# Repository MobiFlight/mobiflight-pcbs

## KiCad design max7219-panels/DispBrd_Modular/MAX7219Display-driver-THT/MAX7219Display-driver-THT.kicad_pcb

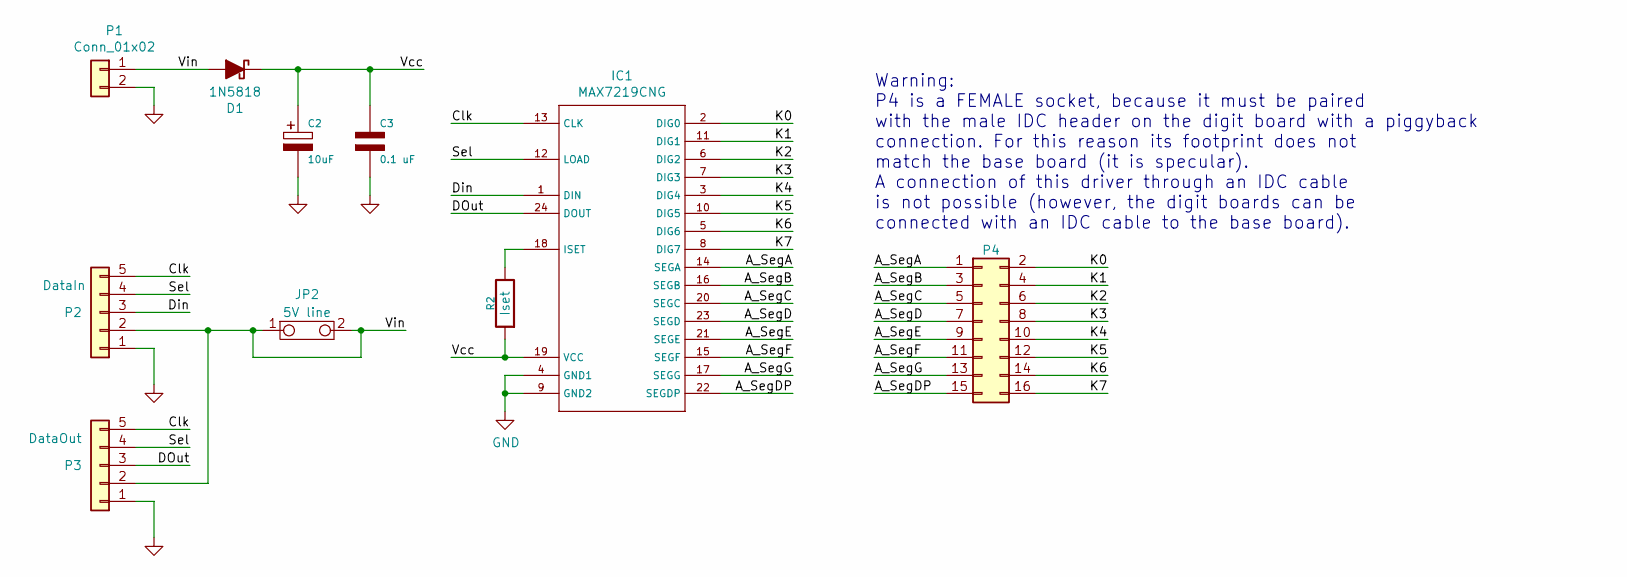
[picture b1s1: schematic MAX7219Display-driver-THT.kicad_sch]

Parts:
C2: 10uF; CP_Radial_D5.0mm_P2.50mm
C3: 0.1 uF; C_1206_3216Metric_Pad1.42x1.75mm_HandSolder
D1: 1N5818; D_SMA_Handsoldering
IC1: MAX7219CNG; DIP-24_W7.62mm_Socket
JP2: 5V line; SolderJumper-2_P1.3mm_Bridged_Pad1.0x1.5mm
P1: Conn_01x02; PinHeader_1x02_P2.54mm_Vertical
P2: DataIn; JST_XH_B5B-XH-A_1x05_P2.50mm_Vertical
P3: DataOut; JST_XH_B5B-XH-A_1x05_P2.50mm_Vertical
P4: Conn_02x08_Odd_Even; PinSocket_2x08_P2.54mm_Vertical
R2: Iset; R_Axial_DIN0207_L6.3mm_D2.5mm_P10.16mm_Horizontal

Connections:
/A_SegA: IC1.14 (SEGA), P4.1
/A_SegB: IC1.16 (SEGB), P4.3
/A_SegC: IC1.20 (SEGC), P4.5
/A_SegD: IC1.23 (SEGD), P4.7
/A_SegDP: IC1.22 (SEGDP), P4.15
/A_SegE: IC1.21 (SEGE), P4.9
/A_SegF: IC1.15 (SEGF), P4.11
/A_SegG: IC1.17 (SEGG), P4.13
/Clk: IC1.13 (CLK), P2.5, P3.5
/DOut: IC1.24 (DOUT), P3.3
/Din: IC1.1 (DIN), P2.3
/K0: IC1.2 (DIG0), P4.2
/K1: IC1.11 (DIG1), P4.4
/K2: IC1.6 (DIG2), P4.6
/K3: IC1.7 (DIG3), P4.8
/K4: IC1.3 (DIG4), P4.10
/K5: IC1.10 (DIG5), P4.12
/K6: IC1.5 (DIG6), P4.14
/K7: IC1.8 (DIG7), P4.16
/Sel: IC1.12 (LOAD), P2.4, P3.4
/Vcc: C2.1, C3.1, D1.1 (K), IC1.19 (VCC), R2.1
/Vin: D1.2 (A), JP2.1, JP2.2, P1.1, P2.2, P3.2
GND: C2.2, C3.2, IC1.4 (GND1), IC1.9 (GND2), P1.2, P2.1, P3.1
unnamed: IC1.18 (ISET), R2.2

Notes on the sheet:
Warning: P4 is a FEMALE socket, because it must be paired with the male IDC header on the digit board with a piggyback connection. For this reason its footprint does not match the base board (it is specular). A connection of this driver through an IDC cable is not possible (however, the digit board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

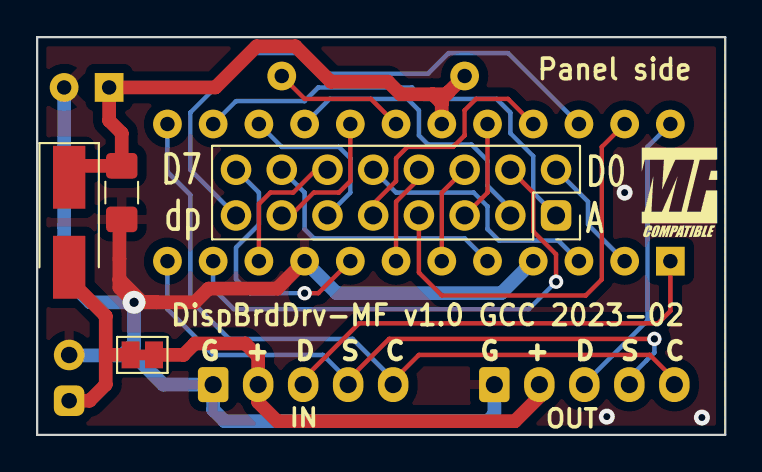
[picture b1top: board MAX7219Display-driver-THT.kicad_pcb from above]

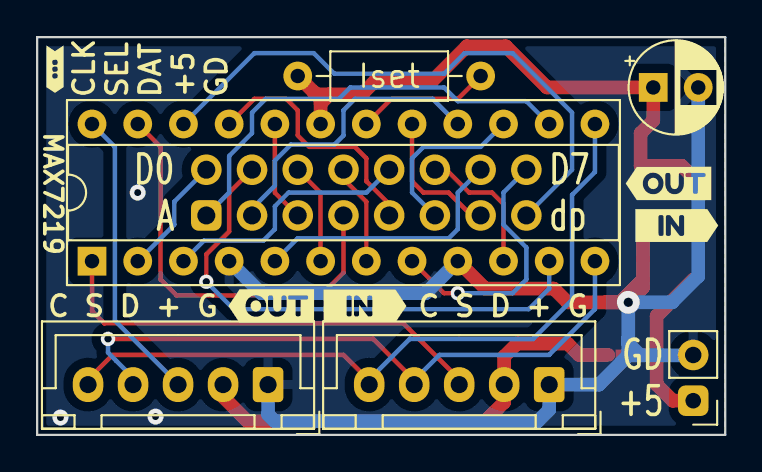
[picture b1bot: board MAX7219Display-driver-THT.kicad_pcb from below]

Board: 2 copper layers, 38.2 x 22.1 mm, 15 parts (11 on the bottom side), 24 nets.

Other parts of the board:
kibuzzard-6403BB05: G***; kibuzzard-6403BB05
kibuzzard-6405E13D: G***; kibuzzard-6405E13D
kibuzzard-6405E14C: G***; kibuzzard-6405E14C
kibuzzard-6405E134: G***; kibuzzard-6405E134
kibuzzard-6405E146: G***; kibuzzard-6405E146

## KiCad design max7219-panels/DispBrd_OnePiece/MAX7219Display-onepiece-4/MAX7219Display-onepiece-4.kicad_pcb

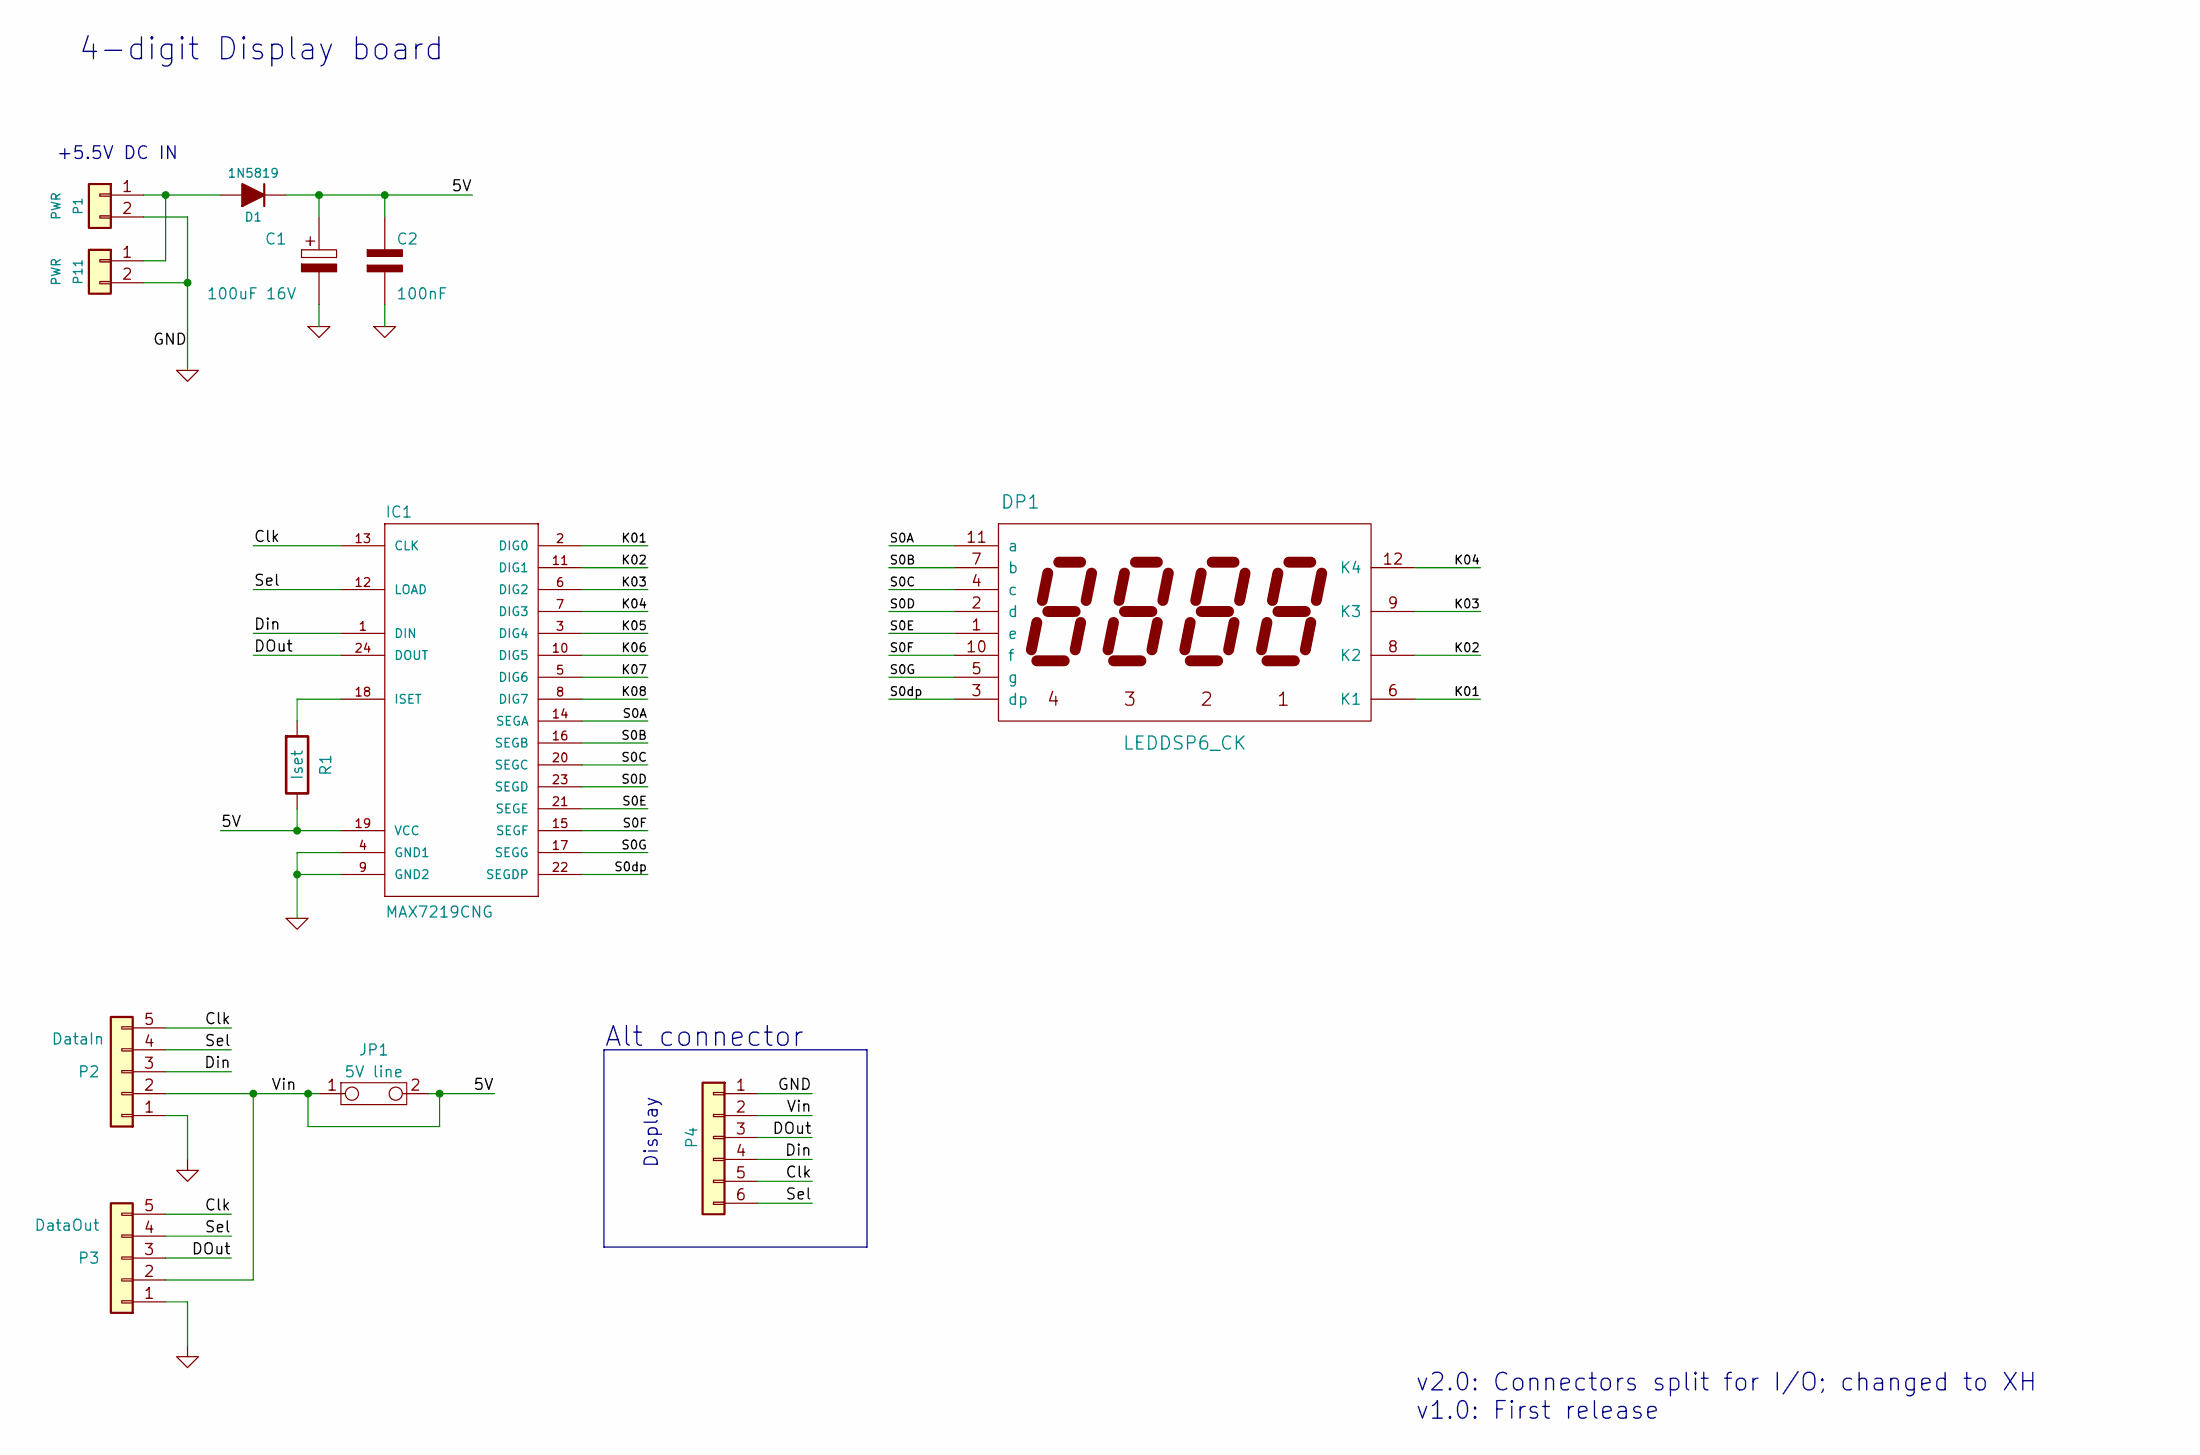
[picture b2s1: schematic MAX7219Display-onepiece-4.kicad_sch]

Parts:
C1: 100uF 16V; CP_Radial_D5.0mm_P2.50mm
C2: 100nF; C_1206_3216Metric_Pad1.33x1.80mm_HandSolder
D1: 1N5819; D_SMA_Handsoldering
DP1: LEDDSP6_CK; Disp7s4x_036
IC1: MAX7219CNG; DIP-24_W7.62mm_Socket
JP1: 5V line; SolderJumper-2_P1.3mm_Bridged_Pad1.0x1.5mm
P1: PWR; PinHeader_1x02_P2.54mm_Vertical
P2: DataIn; JST_XH_B5B-XH-A_1x05_P2.50mm_Vertical
P3: DataOut; JST_XH_B5B-XH-A_1x05_P2.50mm_Vertical
P4: CONN-6; PinHeader_1x06_P2.54mm_Vertical
P11: PWR; HDR2-3.50+3.81mm
R1: Iset; R_Axial_DIN0207_L6.3mm_D2.5mm_P10.16mm_Horizontal

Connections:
/5V: C1.1, C2.1, D1.1 (K), IC1.19 (VCC), JP1.1, JP1.2, P2.2, P3.2, P4.2, R1.2
/Clk: IC1.13 (CLK), P2.5, P3.5, P4.5
/DOut: IC1.24 (DOUT), P3.3, P4.3
/Din: IC1.1 (DIN), P2.3, P4.4
/K01: DP1.6 (K1), IC1.2 (DIG0)
/K02: DP1.8 (K2), IC1.11 (DIG1)
/K03: DP1.9 (K3), IC1.6 (DIG2)
/K04: DP1.12 (K4), IC1.7 (DIG3)
/K05: IC1.3 (DIG4)
/K06: IC1.10 (DIG5)
/K07: IC1.5 (DIG6)
/K08: IC1.8 (DIG7)
/S0A: DP1.11 (a), IC1.14 (SEGA)
/S0B: DP1.7 (b), IC1.16 (SEGB)
/S0C: DP1.4 (c), IC1.20 (SEGC)
/S0D: DP1.2 (d), IC1.23 (SEGD)
/S0E: DP1.1 (e), IC1.21 (SEGE)
/S0F: DP1.10 (f), IC1.15 (SEGF)
/S0G: DP1.5 (g), IC1.17 (SEGG)
/S0dp: DP1.3 (dp), IC1.22 (SEGDP)
/Sel: IC1.12 (LOAD), P2.4, P3.4, P4.6
GND: C1.2, C2.2, IC1.4 (GND1), IC1.9 (GND2), P1.2, P2.1, P3.1, P4.1, P11.2
unnamed: D1.2 (A), P1.1, P11.1
unnamed: IC1.18 (ISET), R1.1

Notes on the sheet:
+5.5V DC IN
Alt connector
v2.0: Connectors split for I/O; changed to XH v1.0: First release
4-digit Display board
Display

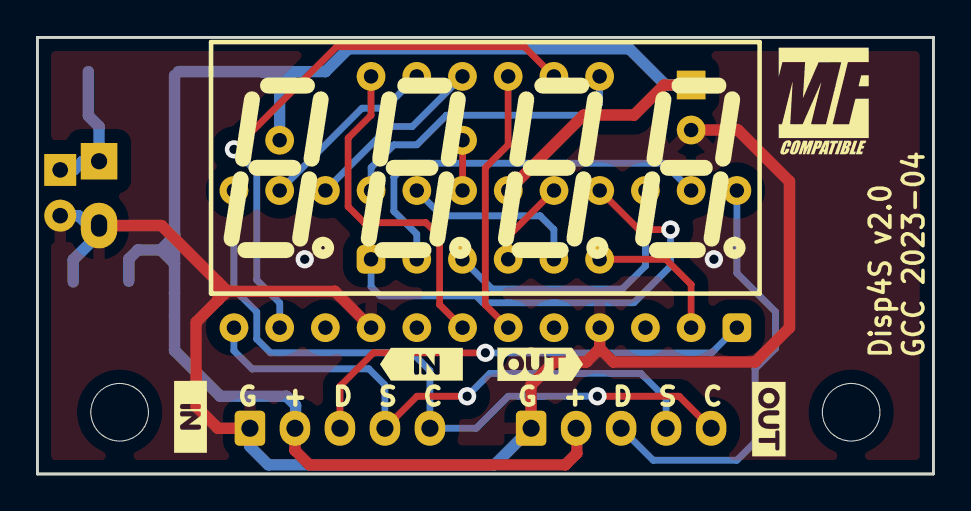
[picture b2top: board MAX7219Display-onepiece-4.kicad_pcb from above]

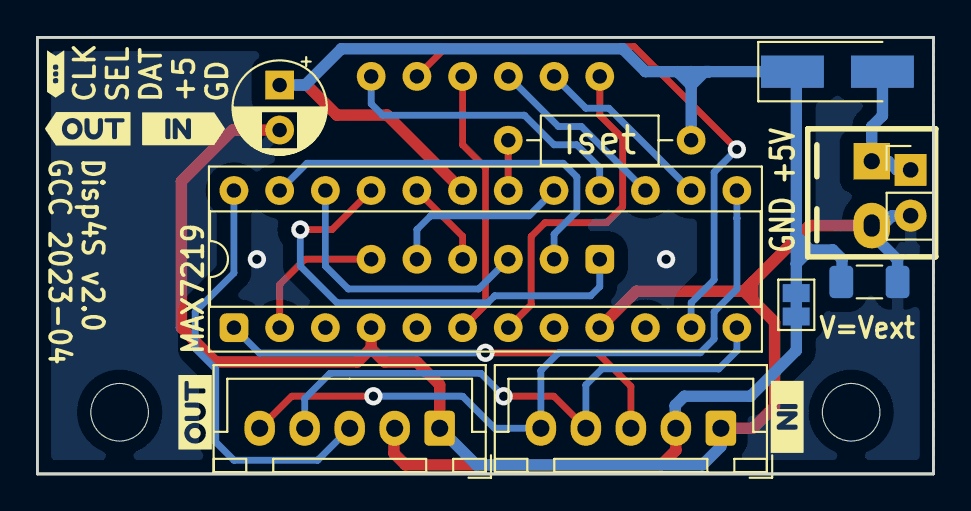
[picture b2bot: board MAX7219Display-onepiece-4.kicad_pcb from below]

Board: 2 copper layers, 49.8 x 24.3 mm, 22 parts (15 on the bottom side), 20 nets.

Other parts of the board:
H1, H2: CONN_1; MountingHole_3.2mm_M3
kibuzzard-643D9E97: G***; kibuzzard-643D9E97
kibuzzard-643D9EA5: G***; kibuzzard-643D9EA5
kibuzzard-643DAD0B: G***; kibuzzard-643DAD0B
kibuzzard-643DAD14, kibuzzard-643DAD14#2: G***; kibuzzard-643DAD14
kibuzzard-643DAD66: G***; kibuzzard-643DAD66
kibuzzard-6403BB05: G***; kibuzzard-6403BB05
kibuzzard-6405E14C: G***; kibuzzard-6405E14C
kibuzzard-6405E146: G***; kibuzzard-6405E146

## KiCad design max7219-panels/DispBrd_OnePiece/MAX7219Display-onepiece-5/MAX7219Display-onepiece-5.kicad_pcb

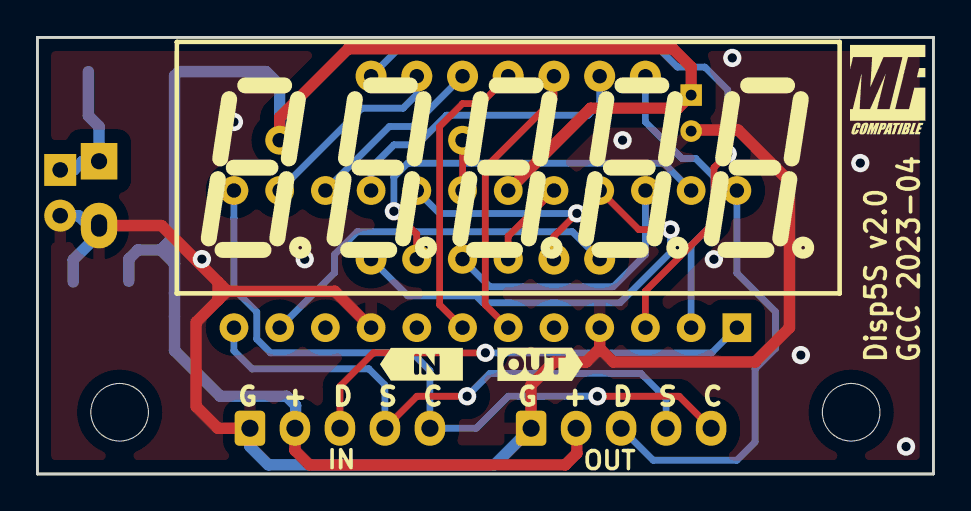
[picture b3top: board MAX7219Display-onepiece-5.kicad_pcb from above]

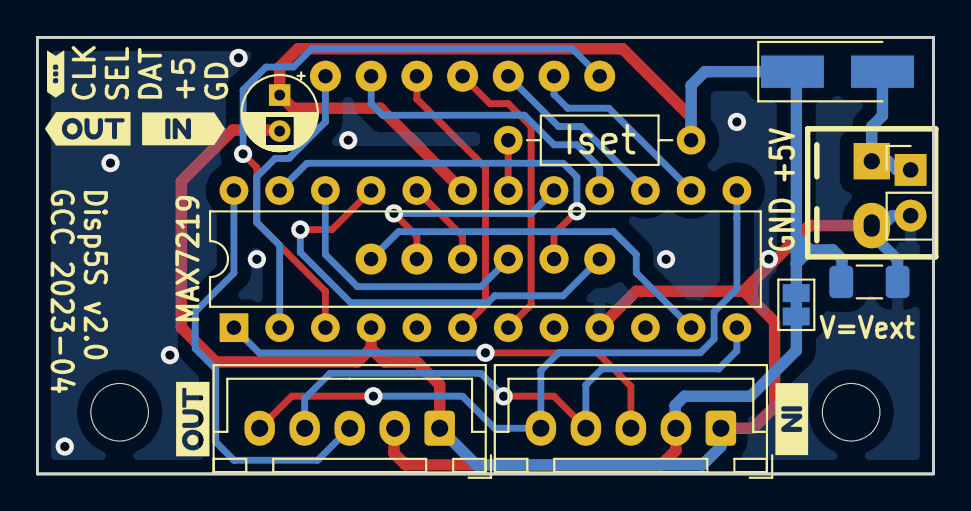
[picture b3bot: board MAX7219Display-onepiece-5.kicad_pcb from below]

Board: 2 copper layers, 49.8 x 24.3 mm, 20 parts (15 on the bottom side), 21 nets.

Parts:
C1: 100uF 16V; CP_Radial_D4.0mm_P2.00mm
C2: 100nF; C_1206_3216Metric_Pad1.33x1.80mm_HandSolder
D1: 1N5819; D_SMA_Handsoldering
DP3: LEDDSP6_CK; Disp7s5x_036
H1, H2: CONN_1; MountingHole_3.2mm_M3
IC1: MAX7219CNG; DIP-24_W7.62mm
JP1: 5V line; SolderJumper-2_P1.3mm_Bridged_Pad1.0x1.5mm
P1: PWR; PinHeader_1x02_P2.54mm_Vertical
P2: DataIn; JST_XH_B5B-XH-A_1x05_P2.50mm_Vertical
P3: DataOut; JST_XH_B5B-XH-A_1x05_P2.50mm_Vertical
P11: PWR; HDR2-3.50+3.81mm
R1: Iset; R_Axial_DIN0207_L6.3mm_D2.5mm_P10.16mm_Horizontal
kibuzzard-643D9E97: G***; kibuzzard-643D9E97
kibuzzard-643D9EA5: G***; kibuzzard-643D9EA5
kibuzzard-643DAA36: G***; kibuzzard-643DAA36
kibuzzard-643DAA60: G***; kibuzzard-643DAA60
kibuzzard-6403BB05: G***; kibuzzard-6403BB05
kibuzzard-6405E14C: G***; kibuzzard-6405E14C
kibuzzard-6405E146: G***; kibuzzard-6405E146

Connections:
/Clk: IC1.13 (CLK), P2.5, P3.5
/DOut: IC1.24 (DOUT), P3.3
/Din: IC1.1 (DIN), P2.3
/K01: DP3.8 (K1), IC1.2 (DIG0)
/K02: DP3.6 (K2), IC1.11 (DIG1)
/K03: DP3.10 (K3), IC1.6 (DIG2)
/K04: DP3.11 (K4), IC1.7 (DIG3)
/K05: DP3.14 (K5), IC1.3 (DIG4)
/S0A: DP3.13 (a), IC1.14 (SEGA)
/S0B: DP3.9 (b), IC1.16 (SEGB)
/S0C: DP3.4 (c), IC1.20 (SEGC)
/S0D: DP3.2 (d), IC1.23 (SEGD)
/S0E: DP3.1 (e), IC1.21 (SEGE)
/S0F: DP3.12 (f), IC1.15 (SEGF)
/S0G: DP3.5 (g), IC1.17 (SEGG)
/S0dp: DP3.3 (dp), IC1.22 (SEGDP)
/Sel: IC1.12 (LOAD), P2.4, P3.4
/Vin: C1.1, C2.1, D1.1 (K), IC1.19 (VCC), JP1.1, JP1.2, P2.2, P3.2, R1.2
GND: C1.2, C2.2, IC1.4 (GND1), IC1.9 (GND2), P1.2, P2.1, P3.1, P11.2
unnamed: D1.2 (A), P1.1, P11.1
unnamed: IC1.18 (ISET), R1.1

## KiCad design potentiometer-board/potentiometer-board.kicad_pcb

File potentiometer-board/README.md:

# Potentiometer board

The potentiometer board fits the same form factor and 20x20mm mounting hole pattern 
as the popular dual encoder board. 

This board features a soldering footprint for an Alps RK09 style potentiometer (the one that looks similar
to common EC11-style rotary encoders) and a three pin JST XH connector for the wires.

This repository contains the KiCad project files and also a gerber zip that can be used to manufacture the board.
But if you are interested in this board, you can also find it in the 
[MobiFlight Community Shop](https://shop.mobiflight.com/product/potentiometer-bundle) bundled with a resin printed
knob set.

Designed by Tuomas Kuosmanen, December 2024
The RK09 potentiometer STEP file was 
[created and shared on GrabCAD by Mart Berghs](https://grabcad.com/library/potentiometer-30).

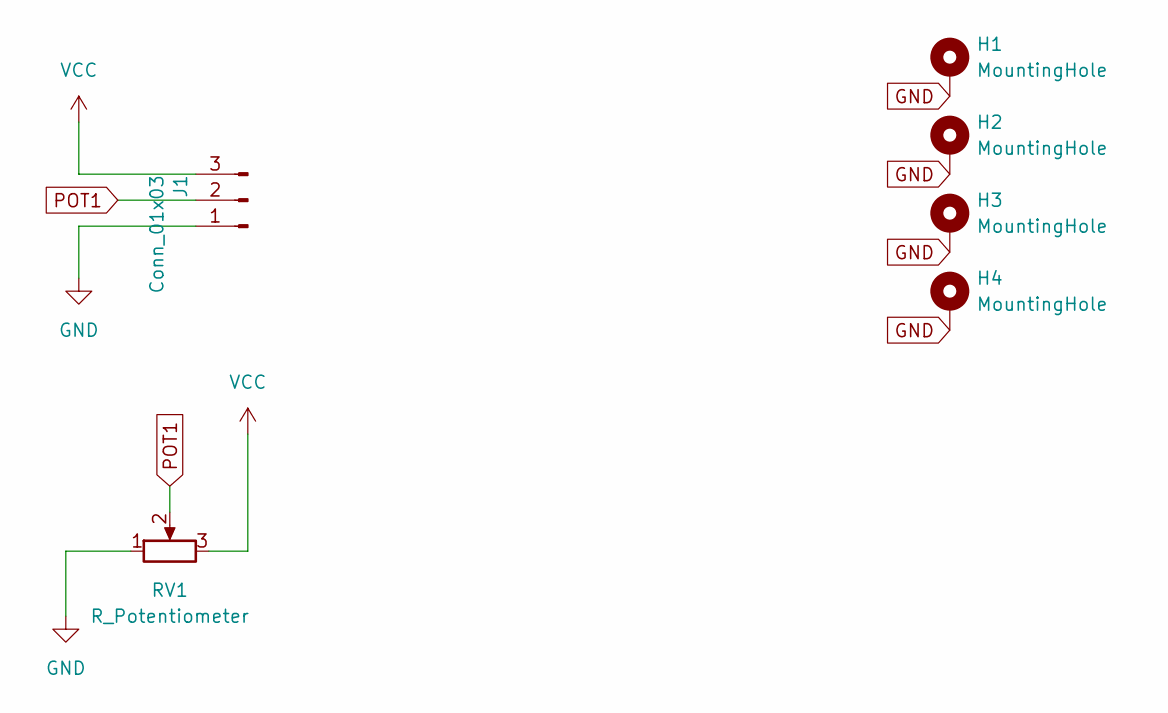
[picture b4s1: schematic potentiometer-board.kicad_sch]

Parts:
H1, H2, H3, H4: MountingHole; MountingHole_3.2mm_M3_ISO14580_Pad_TopBottom
J1: Conn_01x03; JST_XH_B3B-XH-A_1x03_P2.50mm_Vertical; LCSC C144394
RV1: R_Potentiometer; Potentiometer_Alps_RK09K_Single_Vertical

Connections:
GND: H1.1, H2.1, H3.1, H4.1, J1.1, RV1.1
POT1: J1.2, RV1.2
VCC: J1.3, RV1.3

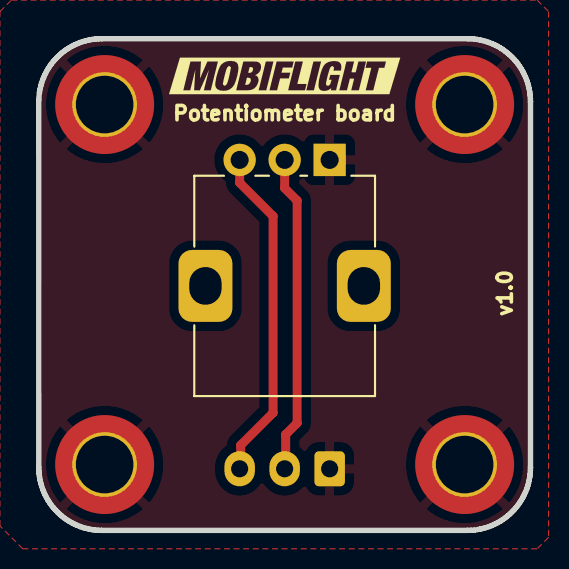
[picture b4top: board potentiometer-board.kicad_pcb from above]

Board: 2 copper layers, 27.3 x 27.3 mm, 7 parts (1 on the bottom side), 3 nets.

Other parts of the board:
kibuzzard-6380ACF0: G***; kibuzzard-6380ACF0

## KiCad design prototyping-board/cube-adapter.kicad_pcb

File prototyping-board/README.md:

# MobiFlight Prototyping Board
The MobiFlight Prototyping Board is a breakout board to learn and experiment with the different input and output devices that are supported by MobiFlight.
The board uses XH JST connectors of different sizes depending on the type of device. These connectors ensure a secure connection and correct orientation of the plugs.

The MobiFlight Prototyping Board is compatible with Arduino Mega 2560 Pro Mini that is attached to the back of the board.

There are two configurations available (latest v2.1):
* Standard - [prototyping-board.mfmc](prototyping-board.mfmc)

  All buttons from `Button 01` to `Button-06` are available, and `Stepper 1` and `Stepper 2` can be both used for steppers 
* Multiplexer - [prototyping-board.multiplexer.mfmc](prototyping-board.multiplexer.mfmc)

  using Stepper 2 as Multiplexer 1 connection, and Button 1 and Button 2 for the signal channels. See [Multiplexer Breakout Board](../breakout-multiplexer/README.md) for more information.

The board is updated based on user feedback, please see the section [older versions](#older-versions) of the config file.
## Devices overview

### Button 1 - 6
Simple buttons that connect with just two wires.

Left pin is Ground, right pin is VCC.

**IMPORTANT** Button 6 is shared with 4th Encoder Push Button

### LEDs 1 - 6
All LEDs are using PWM enabled pins and can be dimmed in MobiFlight.
It is recommended to add an apropriate resistor for you LED. 
[More information about LED output devices](https://docs.mobiflight.com/devices/led/).

Left pin is Ground, right pin is VCC.

### Switch 1 - 5 (On-On)
Connector is designed for On-On switches, two or three position switches.
[More information about buttons and switches](https://docs.mobiflight.com/devices/button-switch/).

* Left pin is GND
* middle pin is Button 1 
* right pin is Button 2

### Switch 6 - 10 (On-On)
Connector is designed for On-On switches, two or three position switches.
[More information about buttons and switches](https://docs.mobiflight.com/devices/button-switch/).

* left pin is GND,
* middle pin is Button 1, 
* right pin is Button 2.

### 7-Segment 1
Connect a 7219MAX-chip based board to this pin.
[More information about 7-segment displays](https://docs.mobiflight.com/devices/seven-segment-display/).

* 1st pin GND,
* 2nd pin VCC,
* 3rd pin DIN,
* 4th pin CS,
* 5th pin CLK

### Encoder 1-4
Connect a Encoder with Push Button function.
[More information about rotary encoders](https://docs.mobiflight.com/devices/encoder/).

* 1st pin GND
* 2nd pin Left Pin (A)
* 3rd pin Right Pin (B)
* 4th pin Push Button

**IMPORTANT** 4th Encoder Push Button is shared with Button 6

### Pot 1 - 3
Connect a Potentiometer or other analog input device.
[More information about potentiometers](https://docs.mobiflight.com/devices/potentiometer/).

* 1st pin GND
* 2nd pin Signal
* 3rd pin VCC

### Shift-Register 1-2
Connect an output shift register.
[More information about output shift registers](https://docs.mobiflight.com/devices/output-shift-register/).

* 1st pin GND
* 2nd pin VCC
* 3rd pin SPI (Latch)
* 4th pin SPI (Clock)
* 5th pin SPI (Data)

### Servo 1-2
Connect a servo. [More information about servos](https://docs.mobiflight.com/devices/servo/).

* 1st pin GND 
* 2nd pin VCC
* 3rd pin DIN

### Stepper 1-2
Connect a stepper. [More information about stepper motors](https://docs.mobiflight.com/devices/stepper-motor/).

* 1st pin GND
* 2nd pin VCC
* 3rd pin Pin1 
* 4th pin Pin2
* 5th pin Pin3
* 6th pin Pin4

Use an additional button pin for the Auto-Zero function.

### LCD Display 1-2
Connect a LCD Display. [More information about LCD displays](https://docs.mobiflight.com/devices/lcd/).

* 1st pin GND
* 2nd pin VCC
* 3rd pin I2C - SDA
* 4th pin I2C - SCL

## Schematic

## Bottom side

## Older versions
For older versions please use the following files:
* 2.0 - [prototyping-board-2.0.mfmc](prototyping-board-2.0.mfmc)

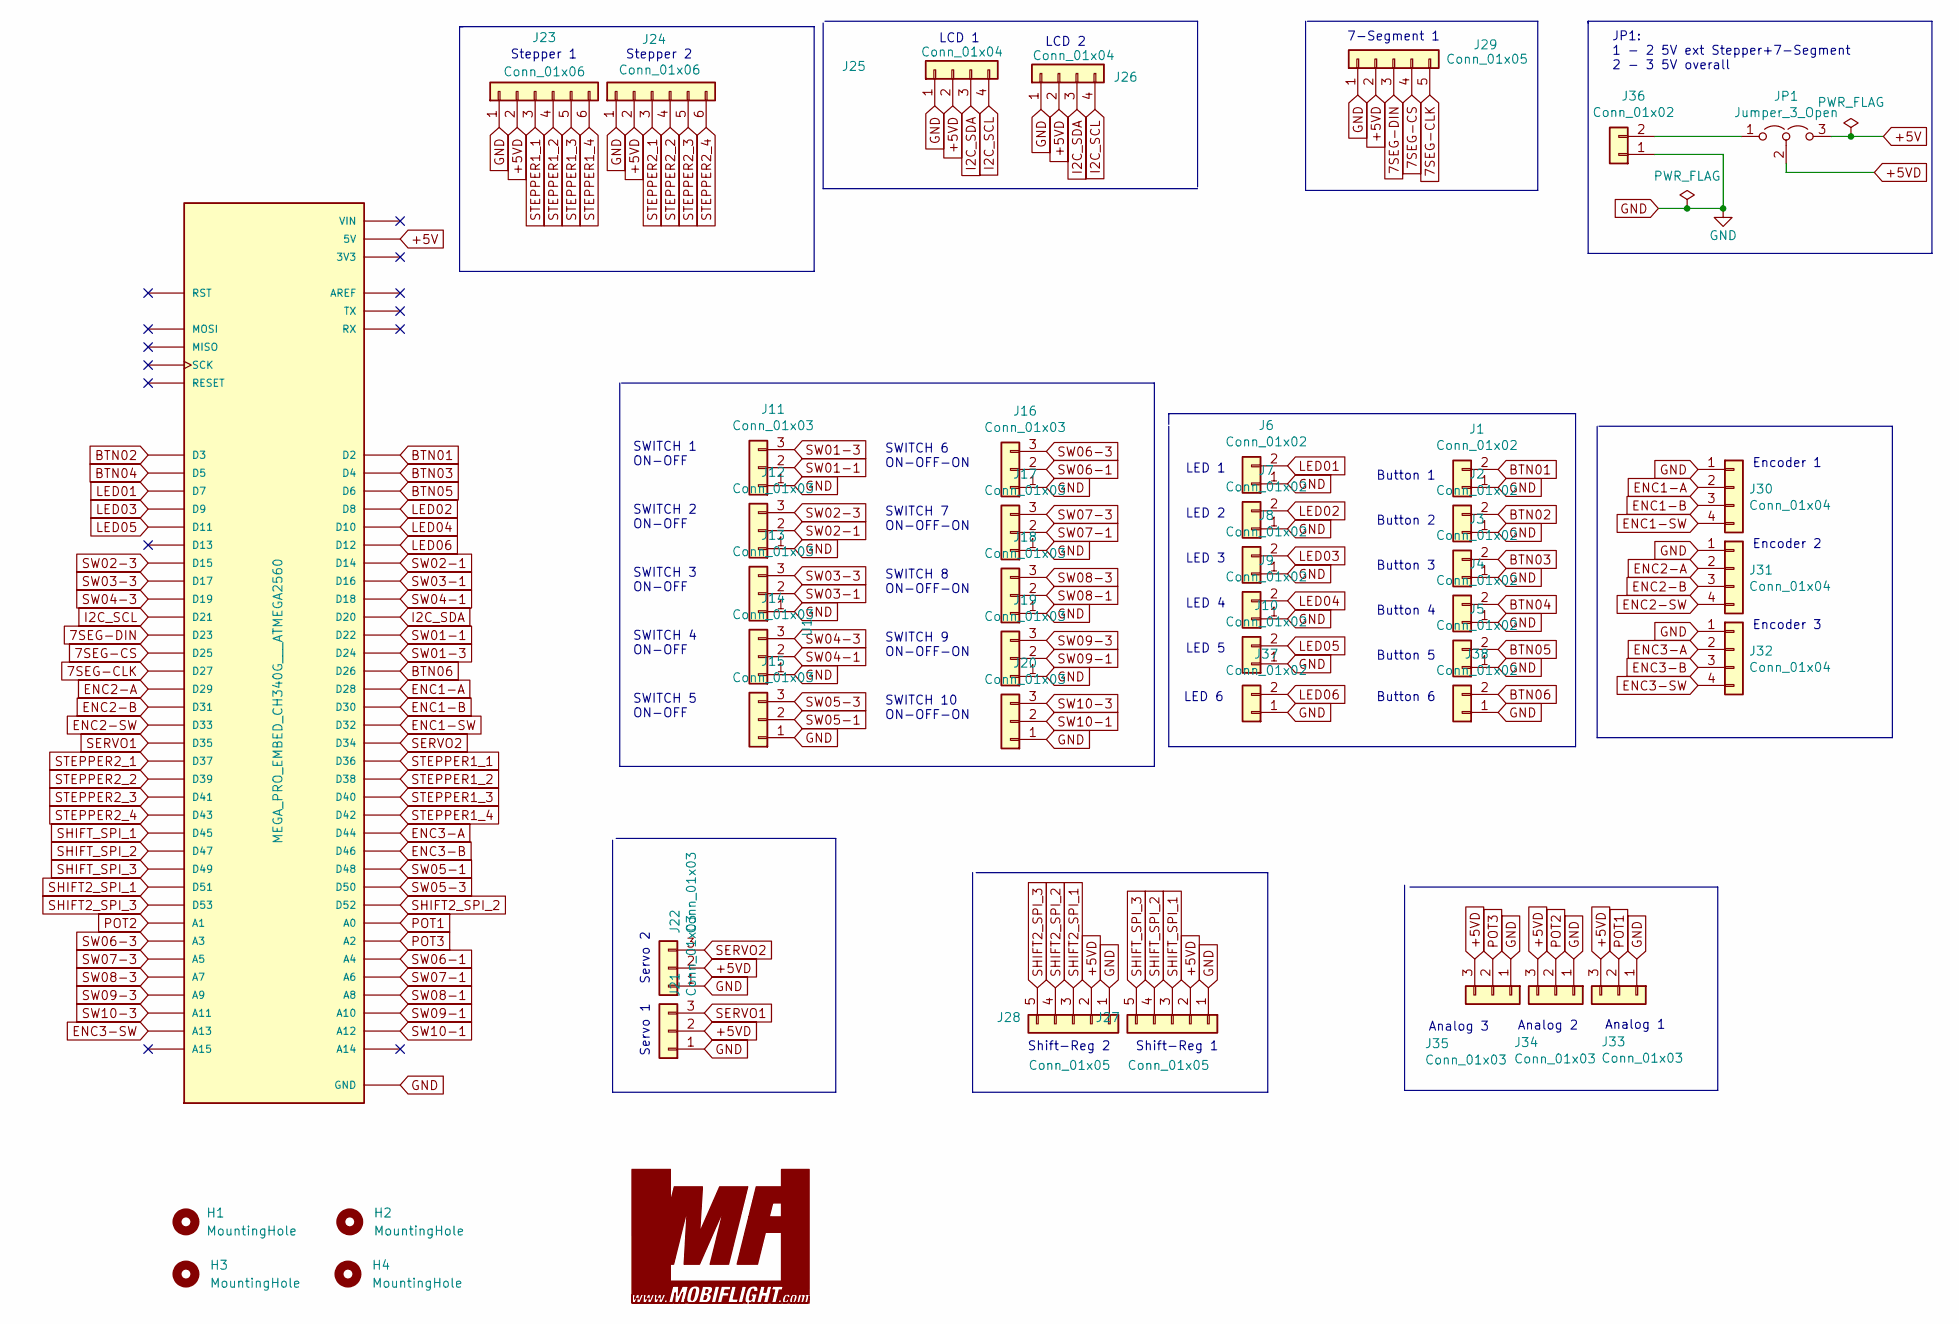
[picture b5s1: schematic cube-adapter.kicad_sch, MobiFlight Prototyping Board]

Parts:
H1, H2, H3, H4: MountingHole; MountingHole_3.5mm
J1, J2, J3, J4, J5, J6, J7, J8, J9, J10, J36, J37, J38: Conn_01x02; JST_XH_B2B-XH-A_1x02_P2.50mm_Vertical
J11, J12, J13, J14, J15, J16, J17, J18, J19, J20, J21, J22, J33, J34, J35: Conn_01x03; JST_XH_B3B-XH-A_1x03_P2.50mm_Vertical
J23, J24: Conn_01x06; JST_XH_B6B-XH-A_1x06_P2.50mm_Vertical
J25, J26, J30, J31, J32: Conn_01x04; JST_XH_B4B-XH-A_1x04_P2.50mm_Vertical
J27, J28, J29: Conn_01x05; JST_XH_B5B-XH-A_1x05_P2.50mm_Vertical
JP1: Jumper_3_Open; PinHeader_1x03_P2.54mm_Vertical
U1: MEGA_PRO_EMBED_CH340G___ATMEGA2560; _ATMEGA2560; PARTREV 12/May/2017

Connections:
7SEG-CLK: J29.5, U1.D27
7SEG-CS: J29.4, U1.D25
7SEG-DIN: J29.3, U1.D23
+5V: JP1.3 (B), U1.5V_1 (5V), U1.5V_2 (5V), U1.5V_3 (5V)
+5VD: J21.2, J22.2, J23.2, J24.2, J25.2, J26.2, J27.2, J28.2, J29.2, J33.3, J34.3, J35.3, JP1.2 (C)
BTN01: J1.2, U1.D2
BTN02: J2.2, U1.D3
BTN03: J3.2, U1.D4
BTN04: J4.2, U1.D5
BTN05: J5.2, U1.D6
BTN06: J38.2, U1.D26
ENC1-A: J30.2, U1.D28
ENC1-B: J30.3, U1.D30
ENC1-SW: J30.4, U1.D32
ENC2-A: J31.2, U1.D29
ENC2-B: J31.3, U1.D31
ENC2-SW: J31.4, U1.D33
ENC3-A: J32.2, U1.D44
ENC3-B: J32.3, U1.D46
ENC3-SW: J32.4, U1.A13
GND: J1.1, J2.1, J3.1, J4.1, J5.1, J6.1, J7.1, J8.1, J9.1, J10.1, J11.1, J12.1, J13.1, J14.1, J15.1, J16.1, J17.1, J18.1, J19.1, J20.1, J21.1, J22.1, J23.1, J24.1, J25.1, J26.1, J27.1, J28.1, J29.1, J30.1, J31.1, J32.1, J33.1, J34.1, J35.1, J36.1, J37.1, J38.1, U1.GND_1 (GND), U1.GND_2 (GND), U1.GND_3 (GND)
I2C_SCL: J25.4, J26.4, U1.D21
I2C_SDA: J25.3, J26.3, U1.D20
LED01: J6.2, U1.D7
LED02: J7.2, U1.D8
LED03: J8.2, U1.D9
LED04: J9.2, U1.D10
LED05: J10.2, U1.D11
LED06: J37.2, U1.D12
unnamed: J36.2, JP1.1 (A)
POT1: J33.2, U1.A0
POT2: J34.2, U1.A1
POT3: J35.2, U1.A2
SERVO1: J21.3, U1.D35
SERVO2: J22.3, U1.D34
SHIFT2_SPI_1: J28.3, U1.D51
SHIFT2_SPI_2: J28.4, U1.D52
SHIFT2_SPI_3: J28.5, U1.D53
SHIFT_SPI_1: J27.3, U1.D45
SHIFT_SPI_2: J27.4, U1.D47
SHIFT_SPI_3: J27.5, U1.D49
STEPPER1_1: J23.3, U1.D36
STEPPER1_2: J23.4, U1.D38
STEPPER1_3: J23.5, U1.D40
STEPPER1_4: J23.6, U1.D42
STEPPER2_1: J24.3, U1.D37
STEPPER2_2: J24.4, U1.D39
STEPPER2_3: J24.5, U1.D41
STEPPER2_4: J24.6, U1.D43
SW01-1: J11.2, U1.D22
SW01-3: J11.3, U1.D24
SW02-1: J12.2, U1.D14
SW02-3: J12.3, U1.D15
SW03-1: J13.2, U1.D16
SW03-3: J13.3, U1.D17
SW04-1: J14.2, U1.D18
SW04-3: J14.3, U1.D19
SW05-1: J15.2, U1.D48
SW05-3: J15.3, U1.D50
SW06-1: J16.2, U1.A4
SW06-3: J16.3, U1.A3
SW07-1: J17.2, U1.A6
SW07-3: J17.3, U1.A5
SW08-1: J18.2, U1.A8
SW08-3: J18.3, U1.A7
SW09-1: J19.2, U1.A10
SW09-3: J19.3, U1.A9
SW10-1: J20.2, U1.A12
SW10-3: J20.3, U1.A11

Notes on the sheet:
SWITCH 6 ON-OFF-ON
Button 6
Servo 1
Analog 3
LCD 2
LED 5
Shift-Reg 1
LED 4
SWITCH 4 ON-OFF
Encoder 3
Button 1
Analog 1
JP1: 1 - 2 5V ext Stepper+7-Segment 2 - 3 5V overall
SWITCH 9 ON-OFF-ON
7-Segment 1
Encoder 2
SWITCH 3 ON-OFF
Analog 2
Servo 2
Encoder 1
SWITCH 8 ON-OFF-ON
LED 1
Stepper 1
Button 3
SWITCH 2 ON-OFF
LED 2
SWITCH 10 ON-OFF-ON
Shift-Reg 2
LED 3
SWITCH 1 ON-OFF
LED 6
Button 5
Button 2
SWITCH 5 ON-OFF
Button 4
LCD 1
Stepper 2
SWITCH 7 ON-OFF-ON

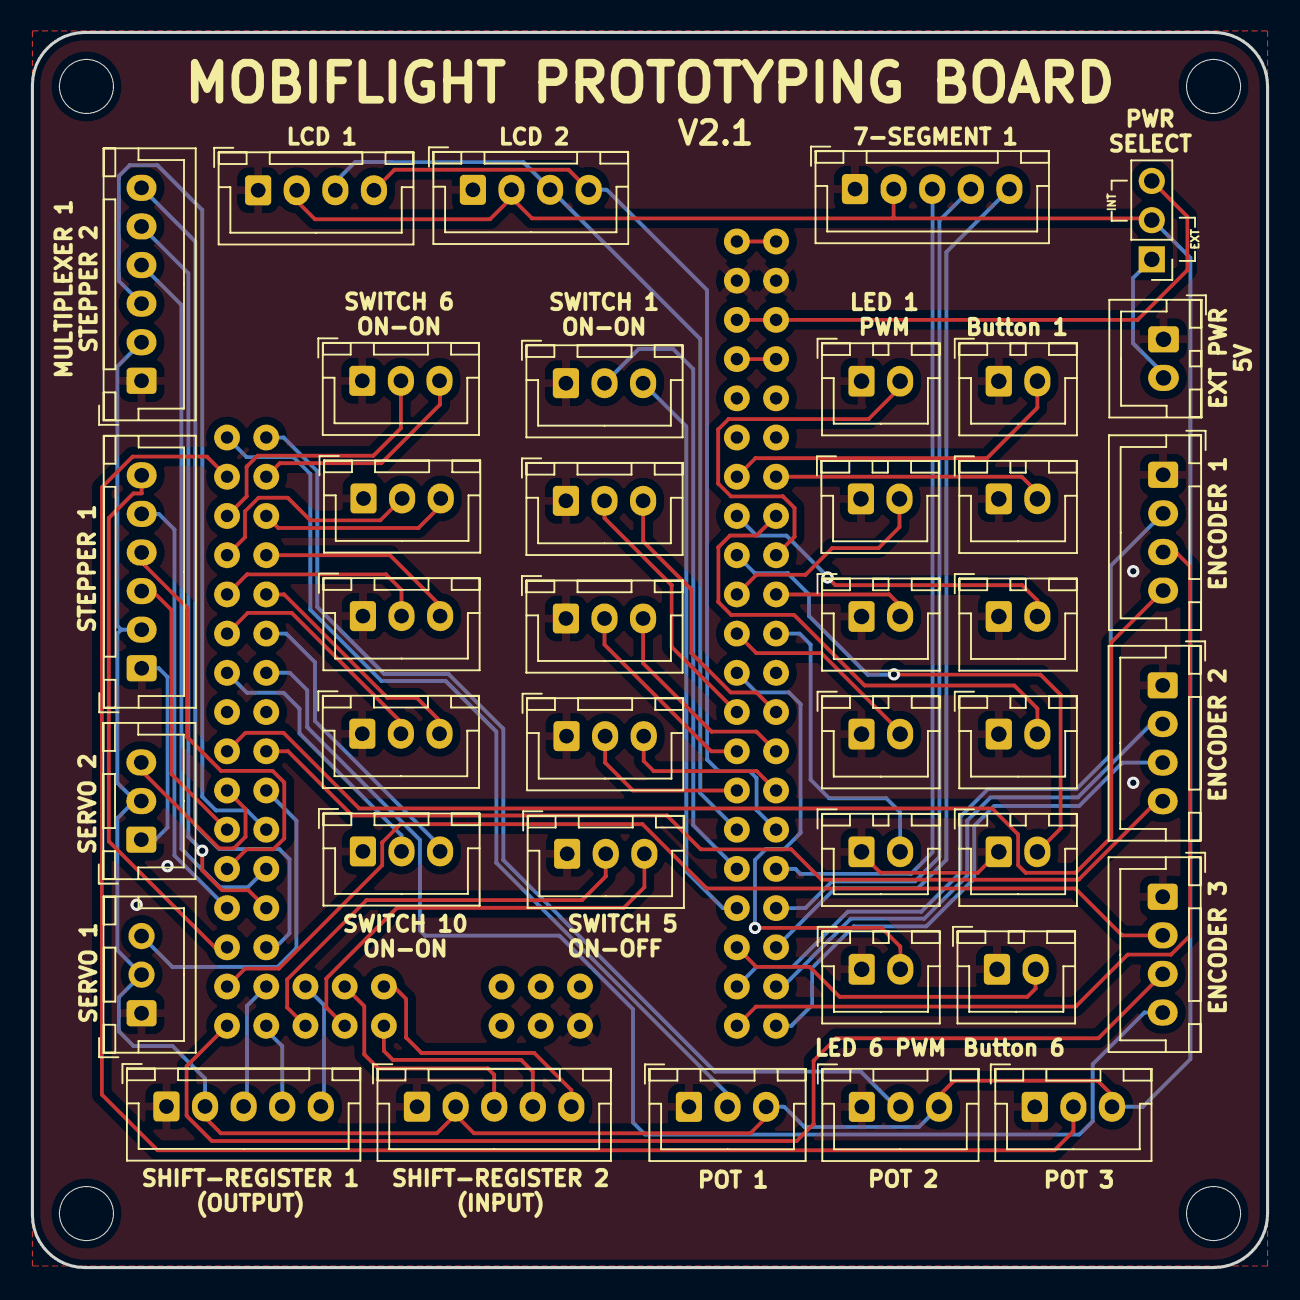
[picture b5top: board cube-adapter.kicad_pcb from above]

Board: 2 copper layers, 80.0 x 80.0 mm, 44 parts (1 on the bottom side), 69 nets.
